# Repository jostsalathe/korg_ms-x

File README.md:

# Korg MS-X

An extreme MONOTRON mod by Soul Machine in form of an SMD PCB.

## credits

The schematics design and build instructions were published by Soul Machine on his project page
[Far Beyond Perception Instruments](https://www.djsoulmachine.com/farbeyondperception/msx.html)
and as 
[PDF here](http://www.djsoulmachine.com/farbeyondperception/msx/MSX-schematics.pdf).

He built it with a lot of perf board and freehand wiring.

Also special thanks to Heiner Büge who convinced me to build this mod with him. He also brought a lot of knowledge about analog synthesizers into this project and I would **not** have been able to develop this project without him!

## Where this project takes over

This project aims to take the design of Soul Machine and develop a neat printed circuit board with SMD components where sensible so that it can be produced and to a large degree even be assembled by cheap manufacturers like [JLCPCB](jlcpcb.com) or [PCBWay](pcbway.com).

## Parts

0805 chip resistors with 1% tolerance shall be used for relatively easy hand soldering.
Most capacitors are cermaic 0805. 100uF (10V) and 47uF (6V3) use 1206 package instead.

### SMD parts

| Part        | Count | Refs                         | JLCPCB # ***extended*** (2021-08-27) |
| ---         | ---   | ---                                                 | ---           |
| 100uF       | 3     | C201, C303, C403                                    | ***C312983*** |
| 10uF        | 10    | C202, C205-C207, C308, C401, C402, C506, C601, C702 | C15850        |
| 47uF        | 2     | C203, C204                                          | C96123        |
| 1uF         | 5     | C301, C302, C304, C305, C701                        | C28323        |
| 100nF       | 7     | C306, C501, C505, C507-C510                         | C49678        |
| 470nF       | 1     | C307                                                | C13967        |
| 22pF        | 1     | C309                                                | C1804         |
| 500pF       | 1     | C404                                                | ***C1747***   |
| 47nF        | 1     | C502                                                | C53134        |
| 4.7nF       | 1     | C503                                                | C1744         |
| 470pF       | 1     | C504                                                | C1743         |
| 100pF       | 1     | C703                                                | C1790         |
| 1N4148      | 4     | D301, D302, D401, D402                              | C2128         |
| 2SC945      | 1     | Q701                                                | ***C181154*** |
| 10k         | 22    | R201, R202, R417, R501, R505-R507, R509, R510, R512, R513, R515, R516, R518, R519, R521, R522, R524, R604, R607, R608, R610 | C17414 |
| 100k        | 43    | R301-R305, R307, R309-R312, R318, R324-R331, R401, R402, R404, R406-R413, R420, R421, R502, R602, R609, R612-R614, R616, R701-R703, R706 | ***C149504*** |
| 33k         | 1     | R306                                                | C17633        |
| 47          | 1     | R308                                                | C17714        |
| 5k6         | 2     | R313, R321                                          | C4382         |
| 4k7         | 1     | R314                                                | C17673        |
| 1M          | 4     | R315, R322, R403, R503                              | C17514        |
| 47k         | 2     | R316, R618                                          | C17713        |
| 56k         | 1     | R317                                                | C17756        |
| 12          | 1     | R319                                                | ***C204200*** |
| 39k         | 2     | R320, R419                                          | C25826        |
| 220k        | 1     | R323                                                | C17556        |
| 22k         | 1     | R405                                                | C17560        |
| 2k2         | 3     | R414-R416                                           | C17520        |
| 180         | 2     | R418, R504                                          | C25270        |
| 1k          | 11    | R508, R511, R514, R517, R520, R523, R525, R601, R605, R619, R707 | C17513 |
| 56          | 1     | R603                                                | C17757        |
| 390         | 1     | R606                                                | C17655        |
| 27k         | 1     | R611                                                | C17593        |
| 330k        | 1     | R615                                                | C17629        |
| 68k         | 1     | R617                                                | C17801        |
| 680k        | 1     | R704                                                | C17797        |
| 470k        | 1     | R705                                                | C17709        |
| 150k        | 1     | R708                                                | C17470        |
| AMS1117-5.0 | 1     | U202                                                | C6187         |
| LMV321      | 3     | U203, U304, U501                                    | C7972         |
| ICL7660S    | 1     | U204                                                | ***C7535***   |
| LM324       | 4     | U301, U302, U401, U402                              | C71035        |
| CD4040BM/TR | 1     | U303                                                | ***C725347*** |
| TL082       | 3     | U601, U602, U701                                    | ***C9385***   |

### THT parts

| Part             | Count | Refs                               |
| ---              | ---   | ---                                |
| 10k trimmer pot  | 5     | RV303, RV401, RV601, RV603, RV605  |
| 100k trimmer pot | 3     | RV502, RV504, RV606                |
| DIP-14 IC socket | 1     | U502                               |

### external parts

| Part               | Count | Refs (optional)                  |
| ---                | ---   | ---                              |
| Korg MONOTRON      | 1     | J101                             |
| LED                | 2     | D403, D501                       |
| DC jack            | 1     | J201                             |
| rotary switch 3P4T | 2     | J301, J601                       |
| rotary switch 4P3T | 1     | J401                             |
| 1/4" mono jack     | 3     | J602, J603, J701                 |
| 10k pot            | 9..11 | RV301, RV501, RV503, (RV505), (RV506), RV507, RV508, RV509, RV510, RV602, RV701 |
| 100k pot           | 1     | RV302                            |
| 20k pot            | 2     | RV402, RV403                     |
| 220k pot           | 1     | RV604                            |
| toggle switch SPST | 1..4  | (SW501), (SW502), SW601, (SW603) |
| mom. switch SPST   | 1     | SW605                            |
| toggle switch SP3T | 0..1  | (SW503)                          |
| toggle switch SPDT | 3..4  | (SW504), SW602, SW604, SW701     |
| mom. switch SPDT   | 0..1  | (SW505)                          |

## Pictures

PCB front:

PCB back:

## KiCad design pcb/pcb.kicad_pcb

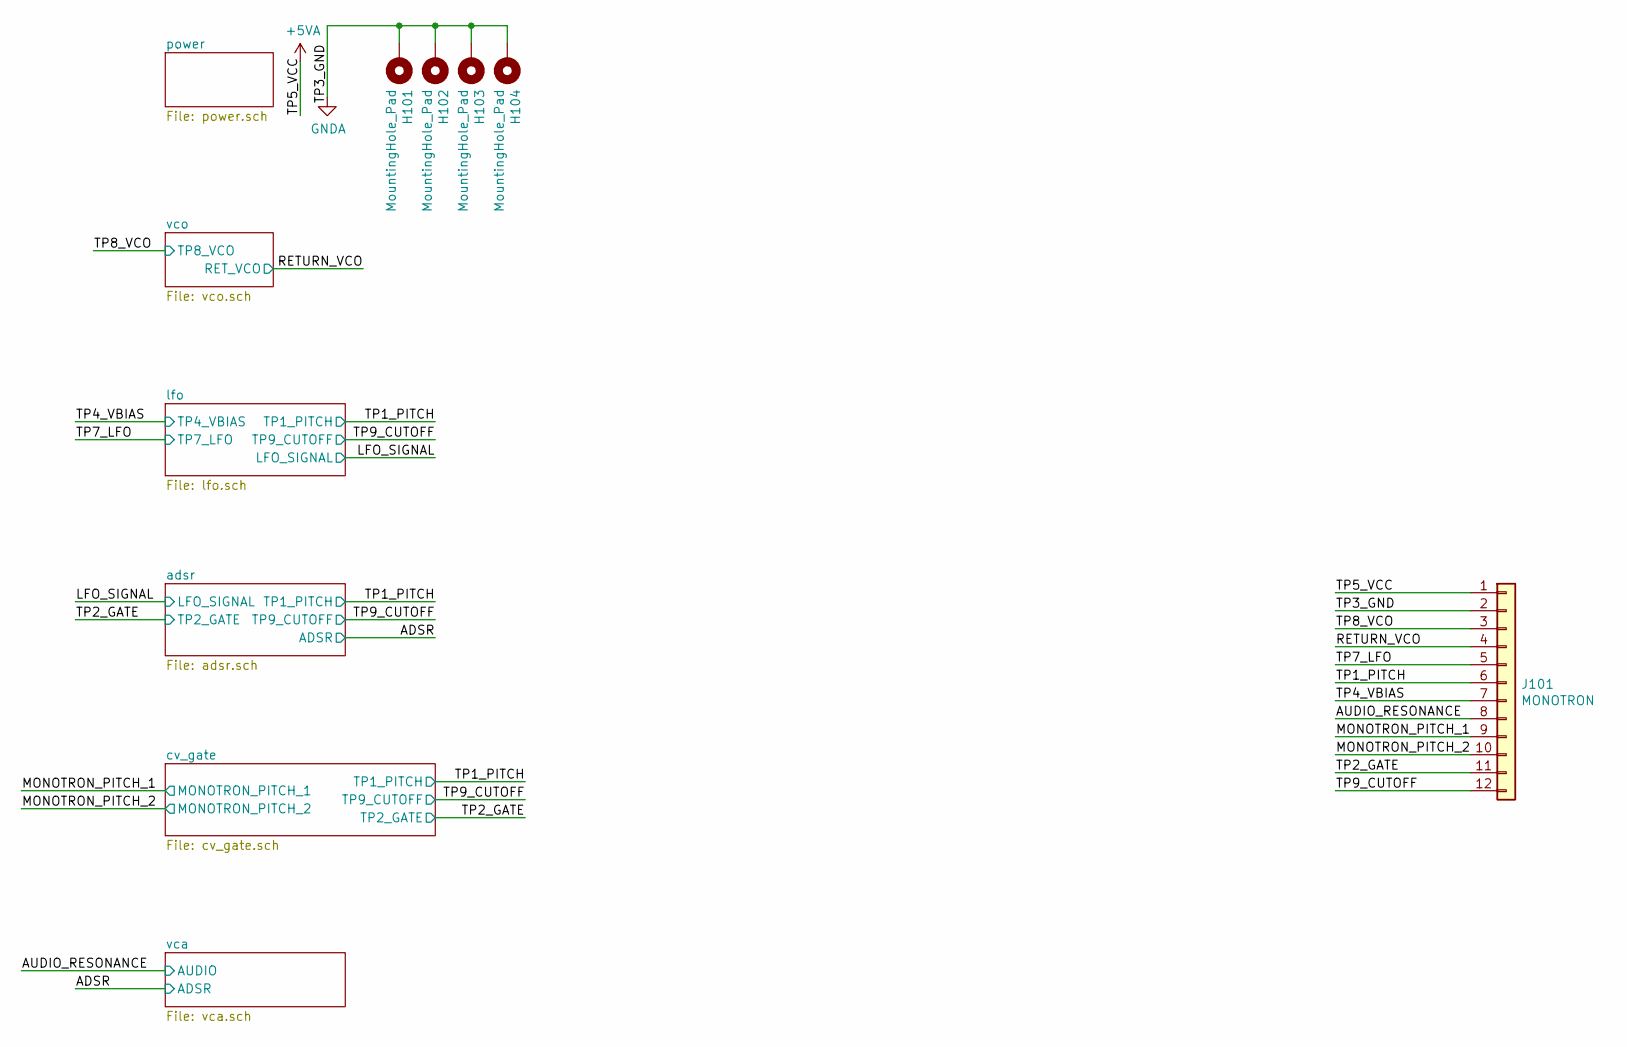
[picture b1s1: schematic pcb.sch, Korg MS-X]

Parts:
H101, H102, H103, H104: MountingHole_Pad; MountingHole_3.2mm_M3_Pad_Via
J101: MONOTRON; PinHeader_1x12_P2.54mm_Vertical

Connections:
+5VA: J101.1; also elsewhere on the board
/AUDIO_RESONANCE: J101.8; also elsewhere on the board
/MONOTRON_PITCH_1: J101.9; also elsewhere on the board
/MONOTRON_PITCH_2: J101.10; also elsewhere on the board
/RETURN_VCO: J101.4; also elsewhere on the board
/TP1_PITCH: J101.6; also elsewhere on the board
/TP2_GATE: J101.11; also elsewhere on the board
/TP4_VBIAS: J101.7; also elsewhere on the board
/TP7_LFO: J101.5; also elsewhere on the board
/TP8_VCO: J101.3; also elsewhere on the board
/TP9_CUTOFF: J101.12; also elsewhere on the board
GNDA: H101.1, H102.1, H103.1, H104.1, J101.2; also elsewhere on the board

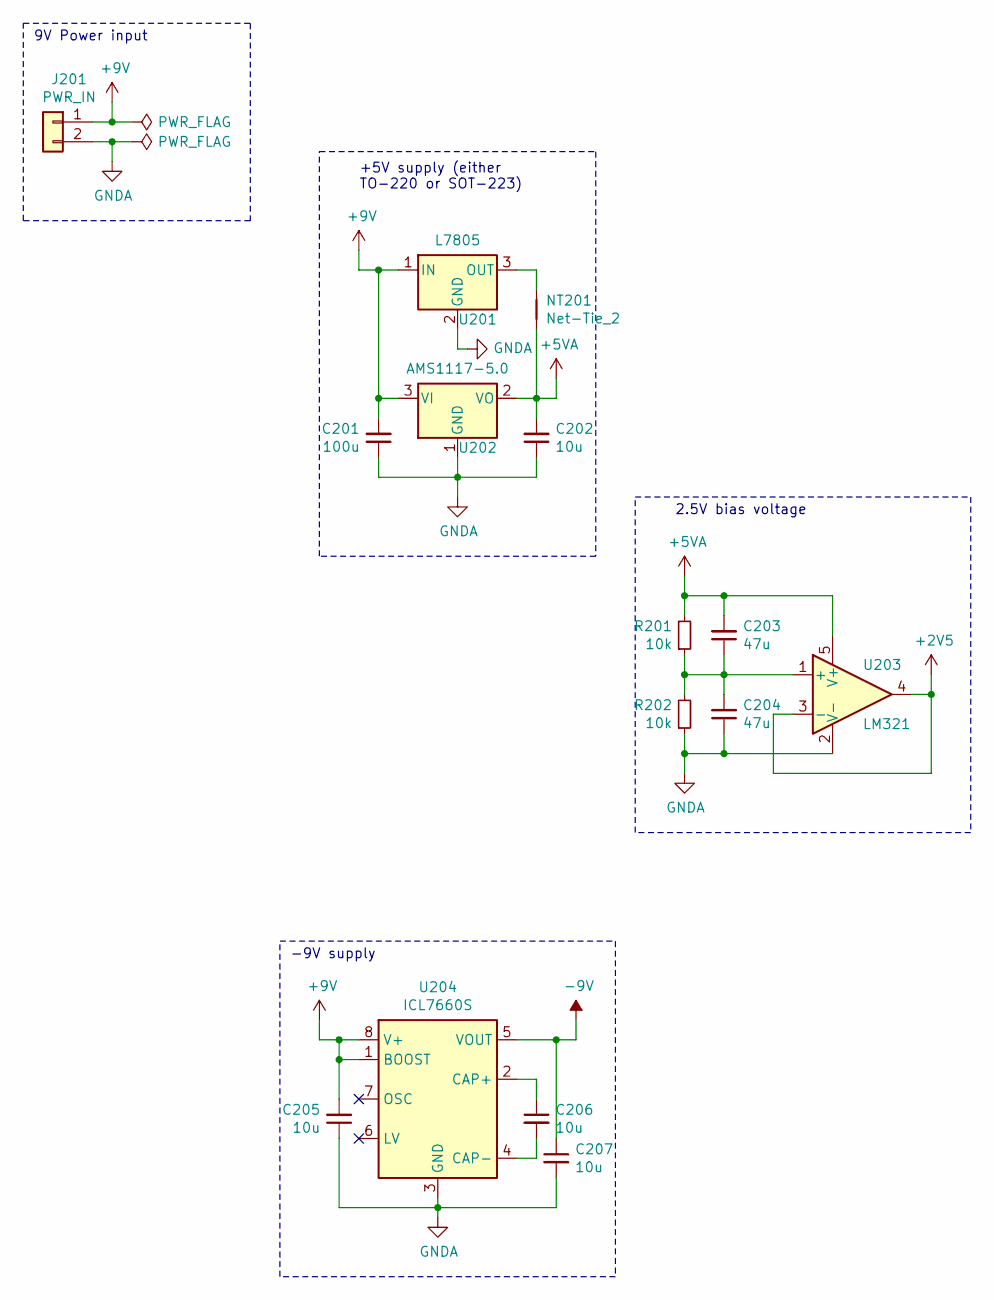
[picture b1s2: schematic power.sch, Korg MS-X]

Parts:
C201: 100u; C_1206_3216Metric_Pad1.42x1.75mm_HandSolder; LCSC C312983
C202, C205, C206, C207: 10u; C_0805_2012Metric_Pad1.18x1.45mm_HandSolder; LCSC C15850
C203, C204: 47u; C_1206_3216Metric_Pad1.42x1.75mm_HandSolder; LCSC C96123
J201: PWR_IN; PinHeader_1x02_P2.54mm_Vertical
NT201: Net-Tie_2; NetTie-2_SMD_Pad0.5mm
R201, R202: 10k; R_0805_2012Metric_Pad1.20x1.40mm_HandSolder; LCSC C17414
U201: L7805; TO-220-3_Horizontal_TabUp
U202: AMS1117-5.0; SOT-223-3_TabPin2; LCSC C6187
U203: LM321; SOT-23-5; LCSC C7972
U204: ICL7660S; SOIC-8-1EP_3.9x4.9mm_P1.27mm_EP2.41x3.3mm_ThermalVias; LCSC C7535

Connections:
+2V5: U203.3 (-), U203.4; also elsewhere on the board
+5VA: C202.2, C203.2, NT201.2, R201.2, U202.2 (VO), U203.5 (V+); also elsewhere on the board
+9V: C201.2, C205.2, J201.1, U201.1 (IN), U202.3 (VI), U204.1 (BOOST), U204.8 (V+); also elsewhere on the board
-9V: C207.1, U204.5 (VOUT); also elsewhere on the board
GNDA: C201.1, C202.1, C204.1, C205.1, C207.2, J201.2, R202.1, U201.2 (GND), U202.1 (GND), U203.2 (V-), U204.3 (GND); also elsewhere on the board
unnamed: C203.1, C204.2, R201.1, R202.2, U203.1 (+)
unnamed: C206.1, U204.2 (CAP+)
unnamed: C206.2, U204.4 (CAP-)
unnamed: NT201.1, U201.3 (OUT)

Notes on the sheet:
9V Power input
-9V supply
+5V supply (either TO-220 or SOT-223)
2.5V bias voltage

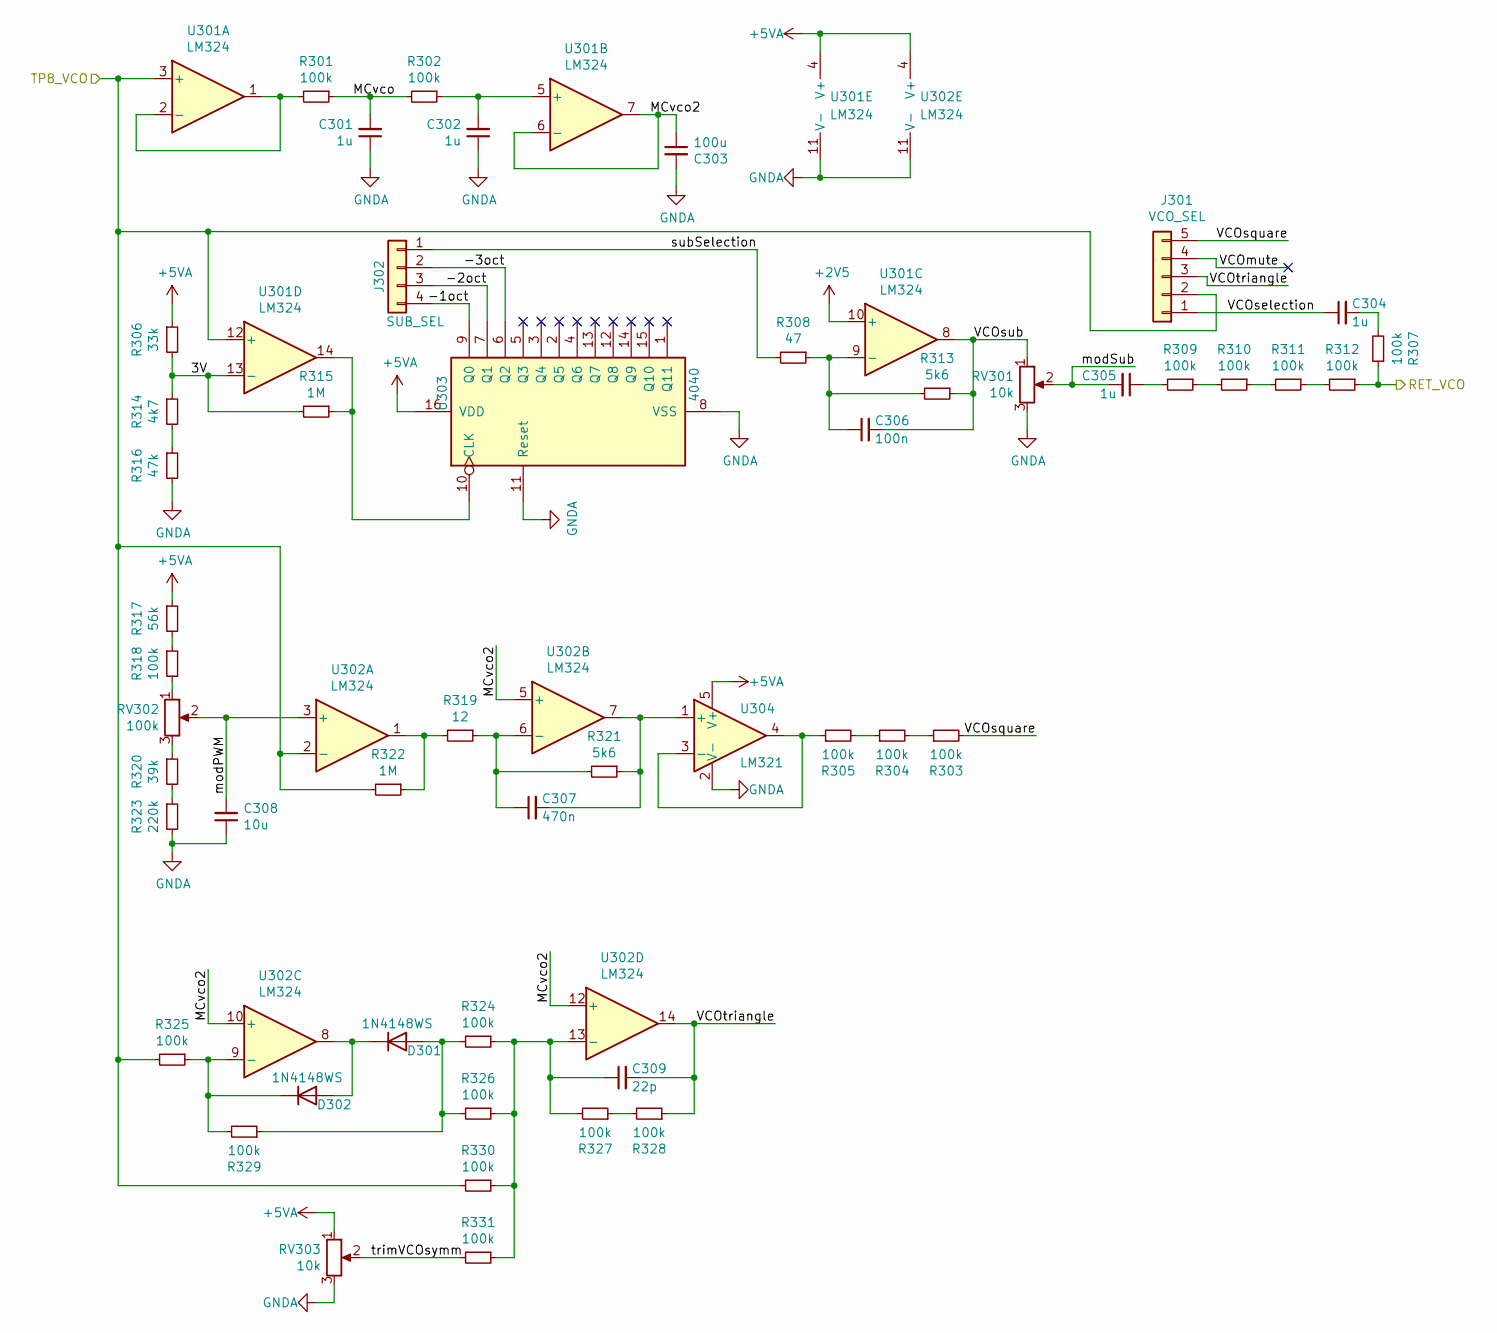
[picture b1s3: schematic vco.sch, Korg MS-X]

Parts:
C301, C302, C304, C305: 1u; C_0805_2012Metric_Pad1.18x1.45mm_HandSolder; LCSC C28323
C303: 100u; C_1206_3216Metric_Pad1.42x1.75mm_HandSolder; LCSC C312983
C306: 100n; C_0805_2012Metric_Pad1.18x1.45mm_HandSolder; LCSC C49678
C307: 470n; C_0805_2012Metric_Pad1.18x1.45mm_HandSolder; LCSC C13967
C308: 10u; C_0805_2012Metric_Pad1.18x1.45mm_HandSolder; LCSC C15850
C309: 22p; C_0805_2012Metric_Pad1.18x1.45mm_HandSolder; LCSC C1804
D301, D302: 1N4148WS; D_SOD-323; LCSC C2128
J301: VCO_SEL; PinHeader_1x05_P2.54mm_Vertical
J302: SUB_SEL; PinHeader_1x04_P2.54mm_Vertical
R301, R302, R303, R304, R305, R307, R309, R310, R311, R312, R318, R324, R325, R326, R327, R328, R329, R330, R331: 100k; R_0805_2012Metric_Pad1.20x1.40mm_HandSolder; LCSC C149504
R306: 33k; R_0805_2012Metric_Pad1.20x1.40mm_HandSolder; LCSC C17633
R308: 47; R_0805_2012Metric_Pad1.20x1.40mm_HandSolder; LCSC C131893
R313, R321: 5k6; R_0805_2012Metric_Pad1.20x1.40mm_HandSolder; LCSC C4382
R314: 4k7; R_0805_2012Metric_Pad1.20x1.40mm_HandSolder; LCSC C17673
R315, R322: 1M; R_0805_2012Metric_Pad1.20x1.40mm_HandSolder; LCSC C17514
R316: 47k; R_0805_2012Metric_Pad1.20x1.40mm_HandSolder; LCSC C17713
R317: 56k; R_0805_2012Metric_Pad1.20x1.40mm_HandSolder; LCSC C17756
R319: 12; R_0805_2012Metric_Pad1.20x1.40mm_HandSolder; LCSC C204200
R320: 39k; R_0805_2012Metric_Pad1.20x1.40mm_HandSolder; LCSC C25826
R323: 220k; R_0805_2012Metric_Pad1.20x1.40mm_HandSolder; LCSC C17556
RV301: 10k; PinHeader_1x03_P2.54mm_Vertical
RV302: 100k; PinHeader_1x03_P2.54mm_Vertical
RV303: 10k; Potentiometer_Bourns_3296W_Vertical
U301, U302: LM324; SOIC-14_3.9x8.7mm_P1.27mm; LCSC C71035
U303: 4040; SOIC-16_3.9x9.9mm_P1.27mm; LCSC C725347
U304: LM321; SOT-23-5; LCSC C7972

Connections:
+2V5: U301.10 (+); also elsewhere on the board
+5VA: R306.1, R317.1, RV303.1, U301.4 (V+), U302.4 (V+), U303.16 (VDD), U304.5 (V+); also elsewhere on the board
/RETURN_VCO: R307.1, R312.1; also elsewhere on the board
/TP8_VCO: J301.2, R322.2, R325.2, R330.2, U301.3 (+), U301.12 (+), U302.2 (-); also elsewhere on the board
/vco/3V: R306.2, R314.1, R315.2, U301.13 (-)
/vco/-1oct: J302.4, U303.9 (Q0)
/vco/-2oct: J302.3, U303.7 (Q1)
/vco/-3oct: J302.2, U303.6 (Q2)
/vco/MCvco: C301.2, R301.1, R302.2
/vco/MCvco2: C303.1, U301.6 (-), U301.7, U302.5 (+), U302.10 (+), U302.12 (+)
/vco/VCOmute: J301.4
/vco/VCOselection: C304.1, J301.1
/vco/VCOsquare: J301.5, R303.2
/vco/VCOsub: C306.2, R313.1, RV301.1, U301.8
/vco/VCOtriangle: C309.2, J301.3, R328.1, U302.14
/vco/modPWM: C308.2, RV302.2, U302.3 (+)
/vco/modSub: C305.2, RV301.2
/vco/subSelection: J302.1, R308.2
/vco/trimVCOsymm: R331.2, RV303.2
GNDA: C301.1, C302.1, C303.2, C308.1, R316.2, R323.2, RV301.3, RV303.3, U301.11 (V-), U302.11 (V-), U303.8 (VSS), U303.11 (Reset), U304.2 (V-); also elsewhere on the board
unnamed: C302.2, R302.1, U301.5 (+)
unnamed: C304.2, R307.2
unnamed: C305.1, R309.2
unnamed: C306.1, R308.1, R313.2, U301.9 (-)
unnamed: C307.1, R319.1, R321.2, U302.6 (-)
unnamed: C307.2, R321.1, U302.7, U304.1 (+)
unnamed: C309.1, R324.1, R326.1, R327.2, R330.1, R331.1, U302.13 (-)
unnamed: D301.1 (K), D302.2 (A), U302.8
unnamed: D301.2 (A), R324.2, R326.2, R329.1
unnamed: D302.1 (K), R325.1, R329.2, U302.9 (-)
unnamed: R301.2, U301.1, U301.2 (-)
unnamed: R303.1, R304.2
unnamed: R304.1, R305.2
unnamed: R305.1, U304.3 (-), U304.4
unnamed: R309.1, R310.2
unnamed: R310.1, R311.2
unnamed: R311.1, R312.2
unnamed: R314.2, R316.1
unnamed: R315.1, U301.14, U303.10 (CLK)
unnamed: R317.2, R318.1
unnamed: R318.2, RV302.1
unnamed: R319.2, R322.1, U302.1
unnamed: R320.1, RV302.3
unnamed: R320.2, R323.1
unnamed: R327.1, R328.2

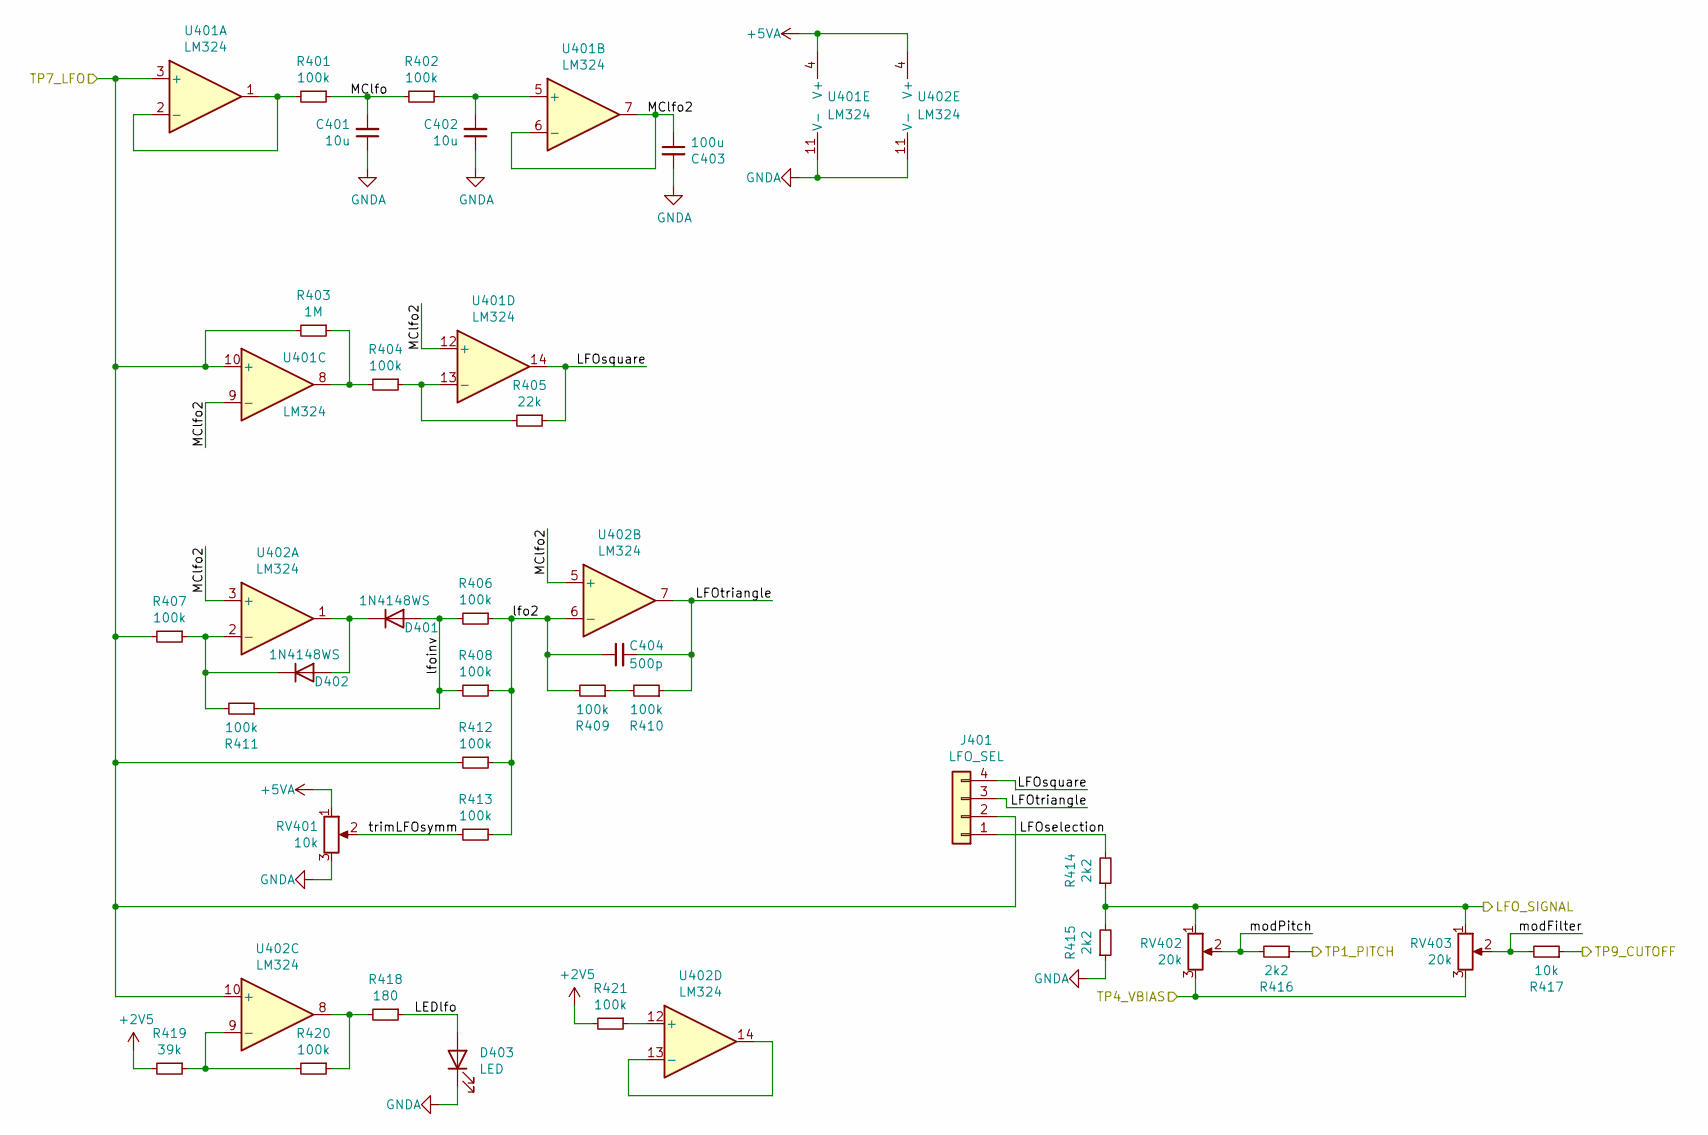
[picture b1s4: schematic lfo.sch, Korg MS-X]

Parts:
C401, C402: 10u; C_0805_2012Metric_Pad1.18x1.45mm_HandSolder; LCSC C15850
C403: 100u; C_1206_3216Metric_Pad1.42x1.75mm_HandSolder; LCSC C312983
C404: 500p; C_0805_2012Metric_Pad1.18x1.45mm_HandSolder; LCSC C1747
D401, D402: 1N4148WS; D_SOD-323; LCSC C2128
D403: LED; LED_D5.0mm
J401: LFO_SEL; PinHeader_1x04_P2.54mm_Vertical
R401, R402, R404, R406, R407, R408, R409, R410, R411, R412, R413, R420, R421: 100k; R_0805_2012Metric_Pad1.20x1.40mm_HandSolder; LCSC C149504
R403: 1M; R_0805_2012Metric_Pad1.20x1.40mm_HandSolder; LCSC C17514
R405: 22k; R_0805_2012Metric_Pad1.20x1.40mm_HandSolder; LCSC C17560
R414, R415, R416: 2k2; R_0805_2012Metric_Pad1.20x1.40mm_HandSolder; LCSC C17520
R417: 10k; R_0805_2012Metric_Pad1.20x1.40mm_HandSolder; LCSC C17414
R418: 180; R_0805_2012Metric_Pad1.20x1.40mm_HandSolder; LCSC C25270
R419: 39k; R_0805_2012Metric_Pad1.20x1.40mm_HandSolder; LCSC C25826
RV401: 10k; Potentiometer_Bourns_3296W_Vertical
RV402, RV403: 20k; PinHeader_1x03_P2.54mm_Vertical
U401, U402: LM324; SOIC-14_3.9x8.7mm_P1.27mm; LCSC C71035

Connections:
+2V5: R419.2, R421.2; also elsewhere on the board
+5VA: RV401.1, U401.4 (V+), U402.4 (V+); also elsewhere on the board
/LFO_SIGNAL: R414.1, R415.2, RV402.1, RV403.1; also elsewhere on the board
/TP1_PITCH: R416.1; also elsewhere on the board
/TP4_VBIAS: RV402.3, RV403.3; also elsewhere on the board
/TP7_LFO: J401.2, R403.2, R407.2, R412.2, U401.3 (+), U401.10 (+), U402.10 (+); also elsewhere on the board
/TP9_CUTOFF: R417.1; also elsewhere on the board
/lfo/LEDlfo: D403.2 (A), R418.1
/lfo/LFOselection: J401.1, R414.2
/lfo/LFOsquare: J401.4, R405.1, U401.14
/lfo/LFOtriangle: C404.2, J401.3, R410.1, U402.7
/lfo/MClfo: C401.2, R401.1, R402.2
/lfo/MClfo2: C403.1, U401.6 (-), U401.7, U401.9 (-), U401.12 (+), U402.3 (+), U402.5 (+)
/lfo/lfo2: C404.1, R406.1, R408.1, R409.2, R412.1, R413.1, U402.6 (-)
/lfo/lfoinv: D401.2 (A), R406.2, R408.2, R411.1
/lfo/modFilter: R417.2, RV403.2
/lfo/modPitch: R416.2, RV402.2
/lfo/trimLFOsymm: R413.2, RV401.2
GNDA: C401.1, C402.1, C403.2, D403.1 (K), R415.1, RV401.3, U401.11 (V-), U402.11 (V-); also elsewhere on the board
unnamed: C402.2, R402.1, U401.5 (+)
unnamed: D401.1 (K), D402.2 (A), U402.1
unnamed: D402.1 (K), R407.1, R411.2, U402.2 (-)
unnamed: R401.2, U401.1, U401.2 (-)
unnamed: R403.1, R404.2, U401.8
unnamed: R404.1, R405.2, U401.13 (-)
unnamed: R409.1, R410.2
unnamed: R418.2, R420.1, U402.8
unnamed: R419.1, R420.2, U402.9 (-)
unnamed: R421.1, U402.12 (+)
unnamed: U402.13 (-), U402.14

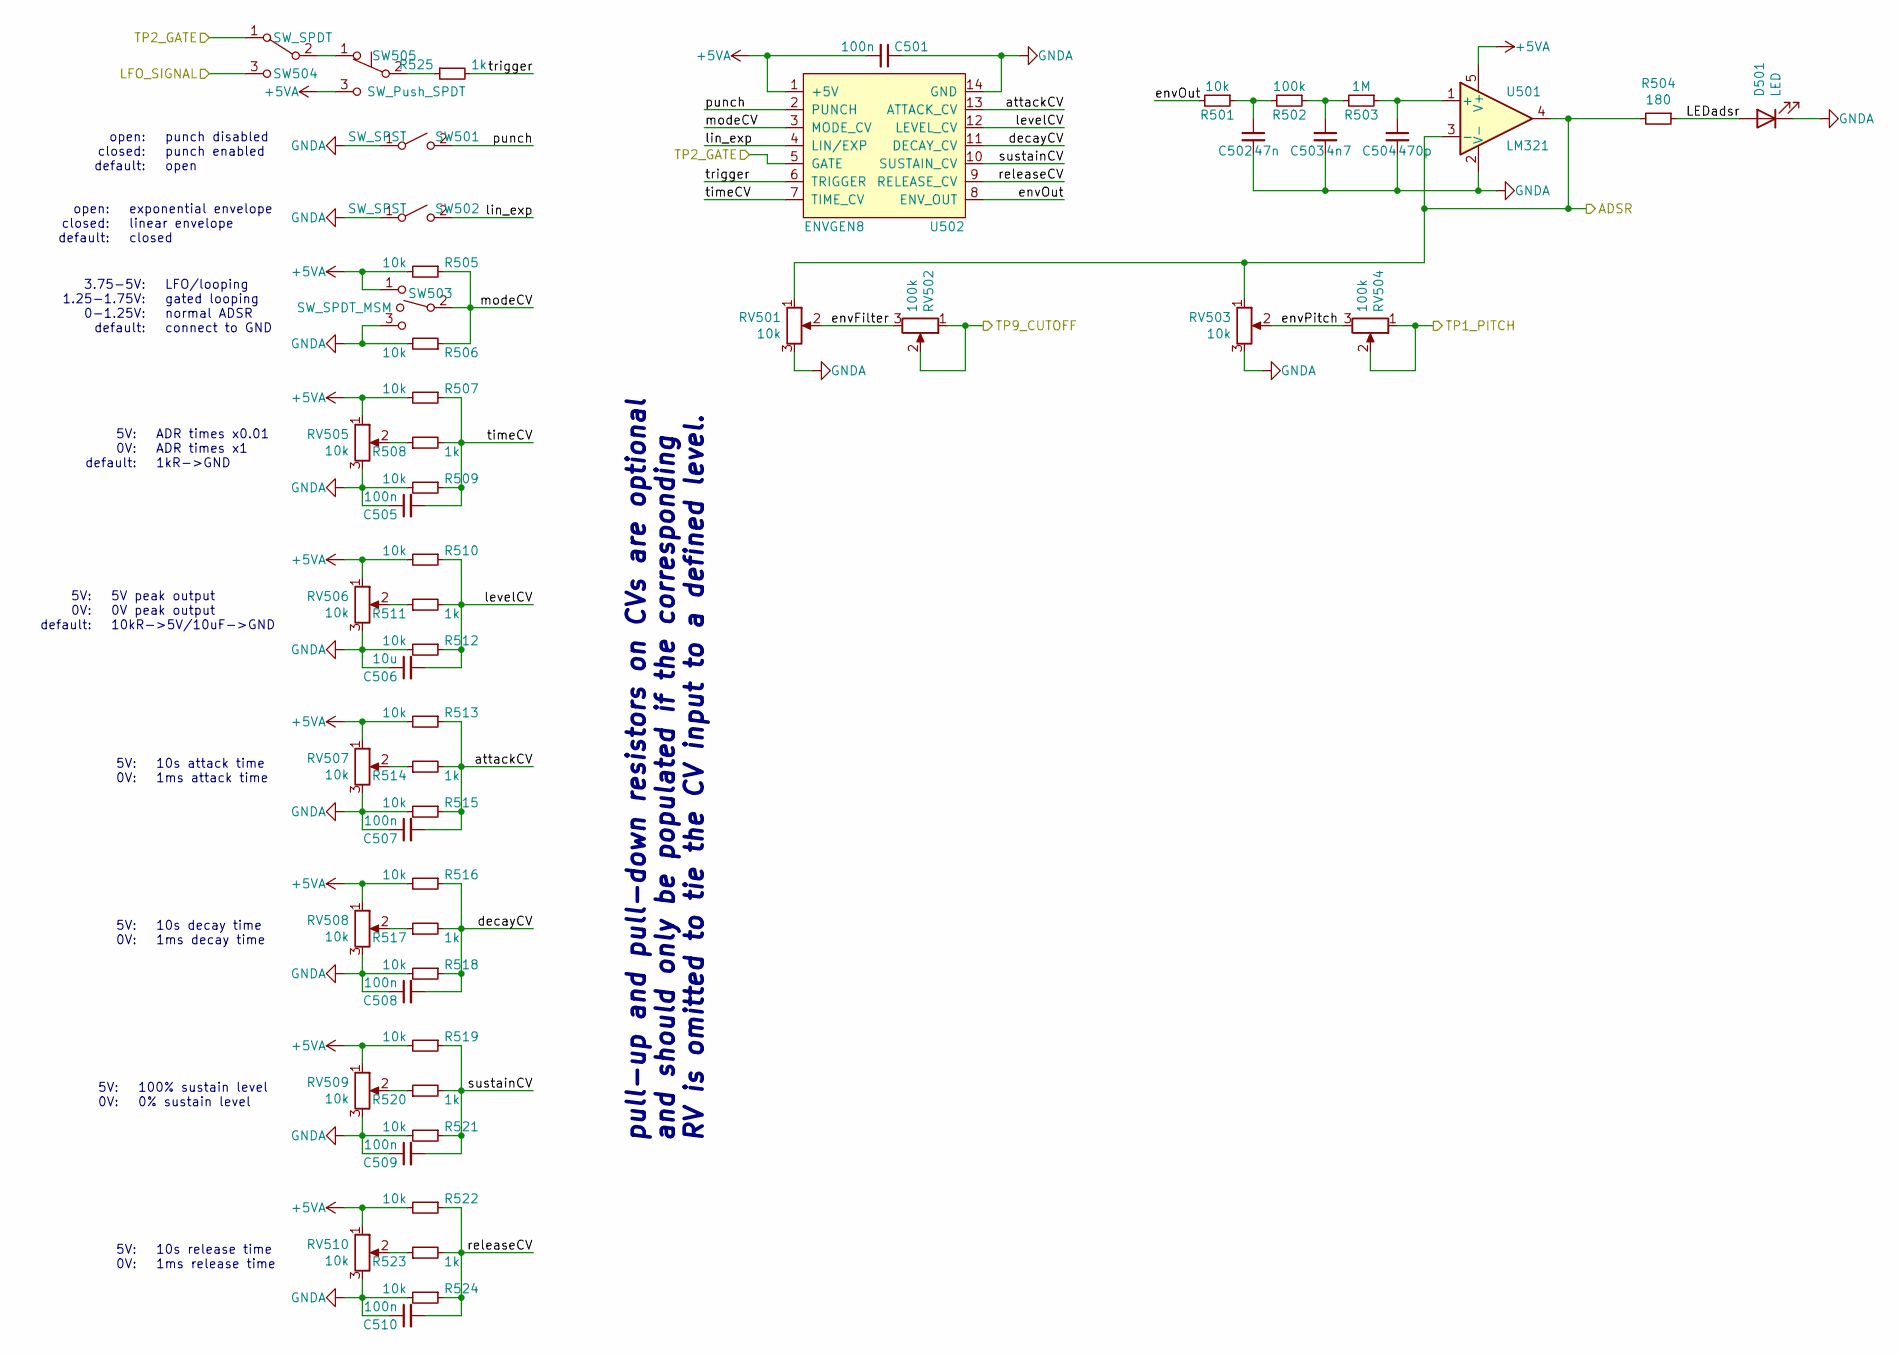
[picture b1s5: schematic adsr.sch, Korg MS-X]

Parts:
C501, C505, C507, C508, C509, C510: 100n; C_0805_2012Metric_Pad1.18x1.45mm_HandSolder; LCSC C49678
C502: 47n; C_0805_2012Metric_Pad1.18x1.45mm_HandSolder; LCSC C53134
C503: 4n7; C_0805_2012Metric_Pad1.18x1.45mm_HandSolder; LCSC C1744
C504: 470p; C_0805_2012Metric_Pad1.18x1.45mm_HandSolder; LCSC C1743
C506: 10u; C_0805_2012Metric_Pad1.18x1.45mm_HandSolder; LCSC C15850
D501: LED; LED_D5.0mm
R501, R505, R506, R507, R509, R510, R512, R513, R515, R516, R518, R519, R521, R522, R524: 10k; R_0805_2012Metric_Pad1.20x1.40mm_HandSolder; LCSC C17414
R502: 100k; R_0805_2012Metric_Pad1.20x1.40mm_HandSolder; LCSC C149504
R503: 1M; R_0805_2012Metric_Pad1.20x1.40mm_HandSolder; LCSC C17514
R504: 180; R_0805_2012Metric_Pad1.20x1.40mm_HandSolder; LCSC C25270
R508, R511, R514, R517, R520, R523, R525: 1k; R_0805_2012Metric_Pad1.20x1.40mm_HandSolder; LCSC C17513
RV501, RV503, RV505, RV506, RV507, RV508, RV509, RV510: 10k; PinHeader_1x03_P2.54mm_Vertical
RV502, RV504: 100k; Potentiometer_Bourns_3296W_Vertical
SW501, SW502: SW_SPST; PinHeader_1x02_P2.54mm_Vertical
SW503: SW_SPDT_MSM; PinHeader_1x03_P2.54mm_Vertical
SW504: SW_SPDT; PinHeader_1x03_P2.54mm_Vertical
SW505: SW_Push_SPDT; PinHeader_1x03_P2.54mm_Vertical
U501: LM321; SOT-23-5; LCSC C7972
U502: ENVGEN8; DIP-14_W7.62mm_Socket_LongPads

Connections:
+5VA: C501.2, R505.2, R507.2, R510.2, R513.2, R516.2, R519.2, R522.2, RV505.1, RV506.1, RV507.1, RV508.1, RV509.1, RV510.1, SW503.1, SW505.3 (C), U501.5 (V+), U502.1 (+5V); also elsewhere on the board
/ADSR: R504.2, RV501.1, RV503.1, U501.3 (-), U501.4; also elsewhere on the board
/LFO_SIGNAL: SW504.3 (C); also elsewhere on the board
/TP1_PITCH: RV504.1, RV504.2; also elsewhere on the board
/TP2_GATE: SW504.1 (A), U502.5 (GATE); also elsewhere on the board
/TP9_CUTOFF: RV502.1, RV502.2; also elsewhere on the board
/adsr/LEDadsr: D501.2 (A), R504.1
/adsr/attackCV: C507.2, R513.1, R514.2, R515.1, U502.13 (ATTACK_CV)
/adsr/decayCV: C508.2, R516.1, R517.2, R518.1, U502.11 (DECAY_CV)
/adsr/envFilter: RV501.2, RV502.3
/adsr/envOut: R501.2, U502.8 (ENV_OUT)
/adsr/envPitch: RV503.2, RV504.3
/adsr/levelCV: C506.2, R510.1, R511.2, R512.1, U502.12 (LEVEL_CV)
/adsr/lin_exp: SW502.2 (B), U502.4 (LIN/EXP)
/adsr/modeCV: R505.1, R506.1, SW503.2, U502.3 (MODE_CV)
/adsr/punch: SW501.2 (B), U502.2 (PUNCH)
/adsr/releaseCV: C510.2, R522.1, R523.2, R524.1, U502.9 (RELEASE_CV)
/adsr/sustainCV: C509.2, R519.1, R520.2, R521.1, U502.10 (SUSTAIN_CV)
/adsr/timeCV: C505.2, R507.1, R508.2, R509.1, U502.7 (TIME_CV)
/adsr/trigger: R525.2, U502.6 (TRIGGER)
GNDA: C501.1, C502.2, C503.2, C504.2, C505.1, C506.1, C507.1, C508.1, C509.1, C510.1, D501.1 (K), R506.2, R509.2, R512.2, R515.2, R518.2, R521.2, R524.2, RV501.3, RV503.3, RV505.3, RV506.3, RV507.3, RV508.3, RV509.3, RV510.3, SW501.1 (A), SW502.1 (A), SW503.3, U501.2 (V-), U502.14 (GND); also elsewhere on the board
unnamed: C502.1, R501.1, R502.2
unnamed: C503.1, R502.1, R503.2
unnamed: C504.1, R503.1, U501.1 (+)
unnamed: R508.1, RV505.2
unnamed: R511.1, RV506.2
unnamed: R514.1, RV507.2
unnamed: R517.1, RV508.2
unnamed: R520.1, RV509.2
unnamed: R523.1, RV510.2
unnamed: R525.1, SW505.2 (B)
unnamed: SW504.2 (B), SW505.1 (A)

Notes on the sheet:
punch disabled punch enabled open
exponential envelope linear envelope closed
LFO/looping gated looping normal ADSR connect to GND
open: closed: default:
3.75-5V: 1.25-1.75V: 0-1.25V: default:
ADR times x0.01 ADR times x1 1kR->GND
5V: 0V: default:
5V peak output 0V peak output 10kR->5V/10uF->GND
10s attack time 1ms attack time
5V: 0V:
10s decay time 1ms decay time
10s release time 1ms release time
100% sustain level 0% sustain level
pull-up and pull-down resistors on CVs are optional and should only be populated if the corresponding RV is omitted to tie the CV input to a defined level.

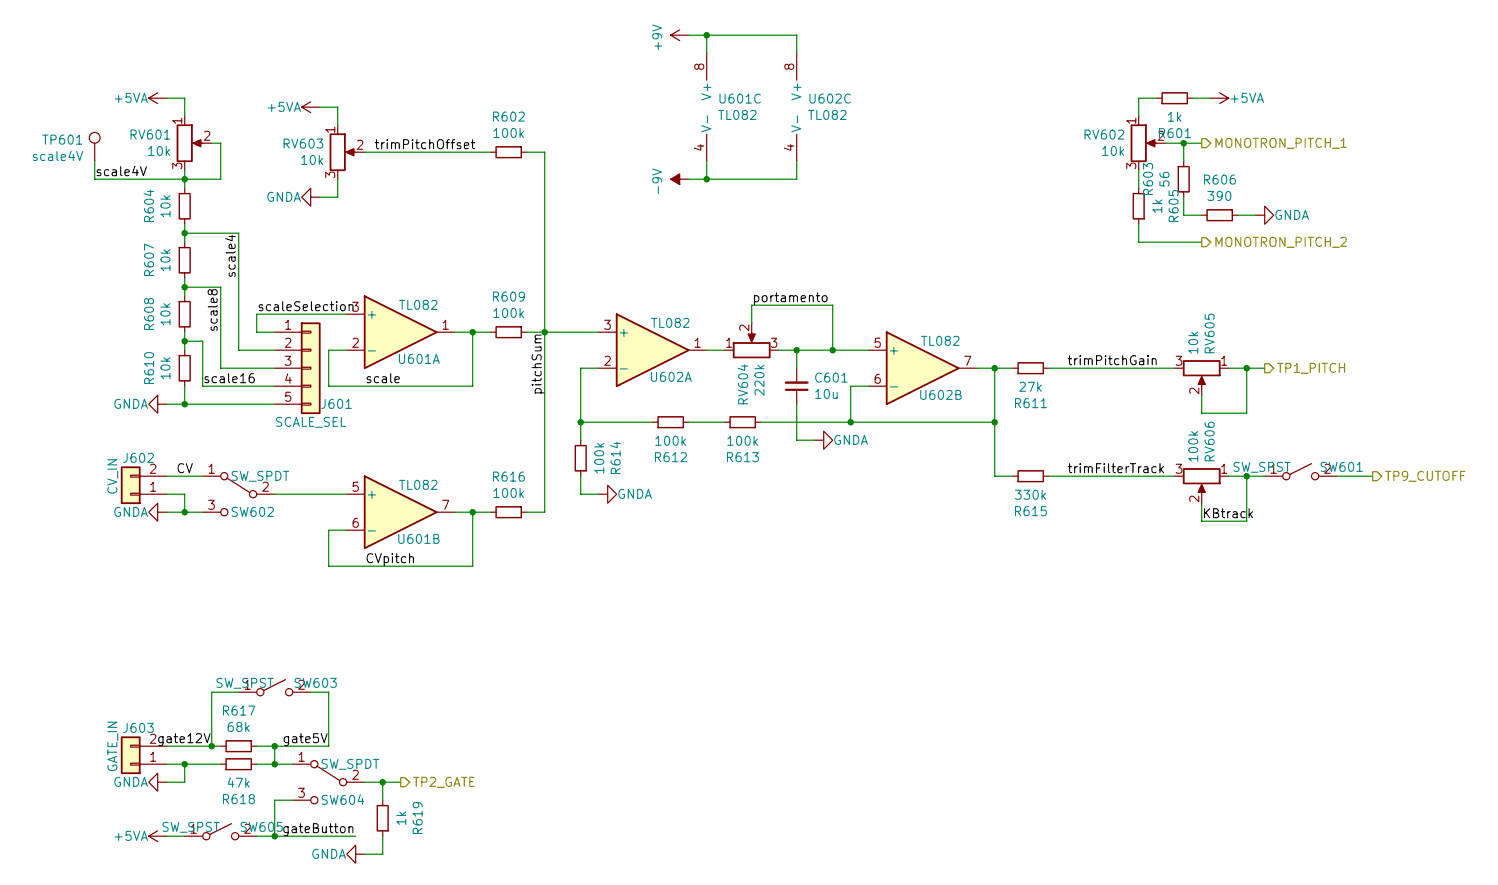
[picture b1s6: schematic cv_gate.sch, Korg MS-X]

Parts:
C601: 10u; C_0805_2012Metric_Pad1.18x1.45mm_HandSolder; LCSC C15850
J601: SCALE_SEL; PinHeader_1x05_P2.54mm_Vertical
J602: CV_IN; PinHeader_1x02_P2.54mm_Vertical
J603: GATE_IN; PinHeader_1x02_P2.54mm_Vertical
R601, R605, R619: 1k; R_0805_2012Metric_Pad1.20x1.40mm_HandSolder; LCSC C17513
R602, R609, R612, R613, R614, R616: 100k; R_0805_2012Metric_Pad1.20x1.40mm_HandSolder; LCSC C149504
R603: 56; R_0805_2012Metric_Pad1.20x1.40mm_HandSolder; LCSC C17757
R604, R607, R608, R610: 10k; R_0805_2012Metric_Pad1.20x1.40mm_HandSolder; LCSC C17414
R606: 390; R_0805_2012Metric_Pad1.20x1.40mm_HandSolder; LCSC C17655
R611: 27k; R_0805_2012Metric_Pad1.20x1.40mm_HandSolder; LCSC C17593
R615: 330k; R_0805_2012Metric_Pad1.20x1.40mm_HandSolder; LCSC C17629
R617: 68k; R_0805_2012Metric_Pad1.20x1.40mm_HandSolder; LCSC C17801
R618: 47k; R_0805_2012Metric_Pad1.20x1.40mm_HandSolder; LCSC C17713
RV601, RV603, RV605: 10k; Potentiometer_Bourns_3296W_Vertical
RV602: 10k; PinHeader_1x03_P2.54mm_Vertical
RV604: 220k; PinHeader_1x03_P2.54mm_Vertical
RV606: 100k; Potentiometer_Bourns_3296W_Vertical
SW601, SW603, SW605: SW_SPST; PinHeader_1x02_P2.54mm_Vertical
SW602, SW604: SW_SPDT; PinHeader_1x03_P2.54mm_Vertical
TP601: scale4V; TestPoint_THTPad_2.0x2.0mm_Drill1.0mm
U601, U602: TL082; SOIC-8_3.9x4.9mm_P1.27mm; LCSC C9385

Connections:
+5VA: R601.2, RV601.1, RV603.1, SW605.1 (A); also elsewhere on the board
+9V: U601.8 (V+), U602.8 (V+); also elsewhere on the board
-9V: U601.4 (V-), U602.4 (V-); also elsewhere on the board
/MONOTRON_PITCH_1: R603.1, RV602.2; also elsewhere on the board
/MONOTRON_PITCH_2: R605.1; also elsewhere on the board
/TP1_PITCH: RV605.1, RV605.2; also elsewhere on the board
/TP2_GATE: R619.2, SW604.2 (B); also elsewhere on the board
/TP9_CUTOFF: SW601.2 (B); also elsewhere on the board
/cv_gate/CV: J602.2, SW602.1 (A)
/cv_gate/CVpitch: R616.2, U601.6 (-), U601.7
/cv_gate/KBtrack: RV606.1, RV606.2, SW601.1 (A)
/cv_gate/gate5V: R617.1, R618.2, SW603.2 (B), SW604.1 (A)
/cv_gate/gate12V: J603.2, R617.2, SW603.1 (A)
/cv_gate/gateButton: SW604.3 (C), SW605.2 (B)
/cv_gate/pitchSum: R602.1, R609.1, R616.1, U602.3 (+)
/cv_gate/portamento: C601.2, RV604.2, RV604.3, U602.5 (+)
/cv_gate/scale: R609.2, U601.1, U601.2 (-)
/cv_gate/scale4: J601.2, R604.2, R607.1
/cv_gate/scale4V: R604.1, RV601.2, RV601.3, TP601.1
/cv_gate/scale8: J601.3, R607.2, R608.1
/cv_gate/scale16: J601.4, R608.2, R610.1
/cv_gate/scaleSelection: J601.1, U601.3 (+)
/cv_gate/trimFilterTrack: R615.2, RV606.3
/cv_gate/trimPitchGain: R611.2, RV605.3
/cv_gate/trimPitchOffset: R602.2, RV603.2
GNDA: C601.1, J601.5, J602.1, J603.1, R606.1, R610.2, R614.1, R618.1, R619.1, RV603.3, SW602.3 (C); also elsewhere on the board
unnamed: R601.1, RV602.1
unnamed: R603.2, R606.2
unnamed: R605.2, RV602.3
unnamed: R611.1, R613.2, R615.1, U602.6 (-), U602.7
unnamed: R612.1, R614.2, U602.2 (-)
unnamed: R612.2, R613.1
unnamed: RV604.1, U602.1
unnamed: SW602.2 (B), U601.5 (+)
